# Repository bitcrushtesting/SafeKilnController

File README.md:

<!--
SPDX-FileCopyrightText: 2026 Bitcrush Testing
SPDX-License-Identifier: GPL-3.0-or-later
-->

# Safe Kiln Controller

An open-source PID controller for electric ceramic and glass kilns, built on the
**ESP32-S3** with **ESP-IDF**.

- **Simple local display**: a 128×64 OLED showing current and target temperature at a glance, plus state, segment progress and rate of rise.
- **Web interface**: served by the device itself. Live dashboard, charts of the logged data, power and energy, and the firing programs the firmware carries. **Observation only**: nothing reachable over the network can start a firing, heat the kiln or change its configuration. Those are done at the kiln.
- **PID with automatic tuning**: relay (Åström–Hägglund) autotune on the real kiln; no manual gain hunting.
- **Firing profiles are compiled in**: the device ships with its curves and nothing edits them, not over the network and not at the kiln. That removes every authoring path and the attack surface each one carries, and it has a real cost: a curve of your own means building a firmware that carries it.
- **Safety first**: thermal runaway, thermocouple failure, shorted-SSR, over-temperature and door-interlock detection, with a safety supervisor that has sole authority over a heat-enable line that decays unless actively refreshed.
- **Current monitoring**: a current transformer turns relay and element failures from slow thermal inferences into fast electrical facts, with the thermal rules retained as an independent backstop.
- **Self-contained**: no SD card, no external database, no account, no filesystem. Logs live in a circular partition on internal flash and programs in a fixed-slot one, each built so a power cut cannot tear a record; web assets are embedded in the firmware. The device makes **one** outbound connection, a daily check for a firmware update that carries nothing about the device and can be turned off at the display.
- **Designed for testability**: all decision logic is hardware-free C++ that runs on a development host against a simulated kiln.

The dashboard mid-firing. Everything on it is read from the device: the `RUN`
and `HEAT` badges, the segment progress, the logged curve. There is no button
here that changes what the kiln is doing, because there is no route behind one
(`SWR-WEB-26`), which is why both notices at the foot of the page say so
plainly.

No kiln was involved. That is the development harness of
[`host/webhost`](firmware/controller/host/webhost) running the real firmware
logic against a simulated one, and it is two commands if you want to click
around yourself:

```sh
cmake -B build-webhost -S firmware/controller/host/webhost && cmake --build build-webhost
./build-webhost/webhost --accel 60 --fire "Bisque cone 06"   # then open http://127.0.0.1:8080
```

`--fire` exists because of the read-only interface: a firing cannot be started
from the browser, so the harness starts one of the built-in examples
(`SWR-PRG-09`) through the same call the local display makes.

## Status

**In development, and not ready to fire a kiln.** The control, safety, storage,
web and interface logic is written and tested. The hardware adapters are
written and **have never been run against a board**. Two things block a
release: the field update path is specified and unbuilt, and local control,
which is now the only control, has never been operated by a person.

433 host tests on the controller and 81 on the independent safety supervisor,
all green plain and under AddressSanitizer and UBSan. `clang-tidy` is clean on
host and target with no suppressions baseline, MC/DC over the supervisor's trip
logic is 100 % against an 80 % floor, the `esp32s3` image builds with zero
warnings at 246 kB (88 % of the OTA slot free), and QEMU boots that image and
fires it. The hardware configuration, which that one compiles out, builds at
908 kB with the browser interface gzipped into it and 56 % of the slot free.

The controller is C++20; the supervisor is C++17, which is the standard
MISRA C++:2023 is written against. What is done, what is not, and what blocks
a release is [`tasklist.md`](tasklist.md), which is kept current and is the
only place that count lives.

You can watch a complete firing, and break it in a dozen ways, without any
hardware at all, see [`docs/simulation.md`](docs/simulation.md):

```sh
tools/run-qemu.sh          # the firmware on an emulated ESP32-S3, kiln simulated
```

or run the logic tests directly:

```sh
cmake -B build-host -S firmware/controller/test/host && cmake --build build-host
ctest --test-dir build-host
```

CI runs eleven jobs: the layering and licence checks, both host suites plain
and under AddressSanitizer and UBSan, a coverage gate, `clang-tidy` on host and
on target, StrictDoc over the requirements, the `esp32s3` build with a size
report and a generated bill of materials, the supervisor suites with MC/DC, the
unit design document with documentation warnings as errors, and a QEMU job that
boots the real image and asserts that the simulated kiln passes 100 degC
without latching a fault. Tagging `v*` builds a release.

## Putting a unit into production

Two tools, in this order, because the order is not interchangeable:

```sh
tools/prod-data.py flash --serial SK1-2026-000042   # identity, a plain write
tools/secure-boot.py provision --key keys/prod.pem  # dry run; add --commit
```

The production data block first, while the device is still freely writable.
Then signing, flashing and lockdown.

The two differ in what they do by default, and the difference is the point.
`prod-data.py` writes unless told `--dry-run`, because its write is a plain
flash write that a reflash undoes. `secure-boot.py` does *nothing* unless told
`--commit`, because most of what it does cannot be undone at all. Both carry a
`--self-test` that needs neither a board nor ESP-IDF.

**`secure-boot.py` burns eFuses, and three of its four steps cannot be undone.**
It refuses to touch a board until its pre-flight passes, demands a differently
worded confirmation for each irreversible step, and sequences them so the device
is left bootable at every point. Read the header of
[`firmware/controller/sdkconfig.secure`](firmware/controller/sdkconfig.secure) before the first run;
the short version is that **losing the signing key means the unit can never run
new firmware again**, and that secure boot stops hostile code running but does
nothing about secrets being read off the flash (`SRR-05`).

### Releasing an update

A third tool, for the other end of the lifecycle. The device fetches one signed
static manifest per channel and verifies it against a key compiled into its own
firmware (`SWR-UPD-09` to `SWR-UPD-16`), and this builds that manifest:

```sh
tools/update-manifest.py keygen --key keys/manifest.pem          # once, then keep it offline
tools/update-manifest.py pubkey --key keys/manifest.pem \
    --header firmware/controller/main/update_pubkey.h            # the half that ships
tools/update-manifest.py sign   --key keys/manifest.pem \
    --image build-esp32s3/safekiln.bin --version 1.4.2 \
    --security --advisory advisories/2026-002.html
tools/update-manifest.py verify --manifest dist/update/stable.json \
    --pubkey keys/manifest.pub.pem --image build-esp32s3/safekiln.bin \
    --running-version 1.4.1
```

The **bill of materials** is generated rather than written
([`tools/sbom.py`](tools/sbom.py), `SWR-NFR-28`): the component list comes from
the build's own `project_description.json`, so it names what was actually
linked, and each licence is scanned from that component's own
`SPDX-License-Identifier` tags, with anything untagged reported as
`NOASSERTION` rather than given a plausible default. CycloneDX 1.6 by default,
SPDX 2.3 with `--format spdx`, both published with every release:

```sh
tools/sbom.py --build-dir firmware/controller/build \
    --image firmware/controller/build/safekiln.bin --format both --strict
```

It has to run where `$IDF_PATH` is, which in CI means inside the IDF container
rather than a step afterwards, because a licence cannot be scanned from a tree
that is not there. The question it exists to answer is "an advisory landed this
morning against mbedTLS 3.6.0, did we ship it", and that cannot be answered
after the fact.

**The manifest key is not the secure boot key, and the tool refuses to let it
be** (`SRR-12`). The secure boot key decides what a provisioned board will
*boot* and its digest is burnt into eFuses, so it can never be rotated; this one
decides what a board will be *offered* and is used on every release. `sign` also
refuses an image with no Secure Boot V2 signature, an image whose chip id is not
this target, a version carrying build metadata, and a security release with no
advisory, because each of those produces a manifest that every device must
reject after downloading it.

It deliberately does not burn `DIS_DOWNLOAD_MODE`. Serial download is
`SWR-UPD-14`'s recovery path, for a unit whose update service is unreachable,
whose new image will not confirm itself, or which has to be downgraded; closing
it as well would make such a unit permanently unfixable.

| Document | Contents |
|---|---|
| [`docs/v-model-process.md`](docs/v-model-process.md) | The development process: the V-model levels, which document holds each, the relations between them, and an honest record of which levels exist and which do not. |
| [`docs/01_user_req.sdoc`](docs/01_user_req.sdoc) | User requirements: the target markets (the European Union), the regulatory framework that follows from them with instrument numbers and editions, the user needs with their acceptance criteria, and the project constraints. |
| [`docs/02_system_req.sdoc`](docs/02_system_req.sdoc) | System requirements: the hardware interface, the four safety requirements that hardware discharges, and the assumptions about the environment the system is placed in. |
| [`docs/03_software_req.sdoc`](docs/03_software_req.sdoc) | Software requirements: the functional, safety, non-functional and testability requirements, each with an identifier and a verification method. |
| [`docs/04_software_arch.sdoc`](docs/04_software_arch.sdoc) | Software architecture: the 22 decisions the design rests on, each with the requirement that drove it and the cost it carries. |
| [`docs/safety.sdoc`](docs/safety.sdoc) | Hazards, safety goals and residual risks, each with an identifier, and the chain between them as checked relations: which hazards a goal mitigates, which requirements realise it, and which risk its layers leave. |
| [`docs/safety.md`](docs/safety.md) | Safety concept: the system boundary, the layered protection concept and the independence claimed between layers, detection coverage and timing, the reaction and recovery sequence, and the obligations on the installer and on anyone changing the design. |
| [`docs/security.sdoc`](docs/security.sdoc) | Assets, adversaries, threats, security goals, residual risks and open questions, each with an identifier, and the chain between them as checked relations: which asset a threat is aimed at, which safety hazard it reaches, which goal answers it, and what each goal's implementation status actually is. |
| [`docs/security.md`](docs/security.md) | Security concept: scope, the attack surface and trust boundaries, the physical boundary and why the supervisor's debug port is deliberately open, the update path and why it points outwards, why a security compromise here is a safety event, what the implementation already gets right, the obligations on the owner and on whoever implements the HTTP transport, the verification status, and an inventory of what the Cyber Resilience Act still requires. |
| [`SECURITY.md`](SECURITY.md) | The security policy: where to report a vulnerability and what happens then, the single point of contact and the reporting obligations behind it, the supported versions and the support period, how a fix reaches a device, and what is already documented as a residual risk so a report need not restate it. |
| [`docs/architecture.md`](docs/architecture.md) | Architecture prose: component decomposition, task and timing design, control and safety algorithms, persistence and flash-endurance design, REST API, and the build and test architecture. |
| [`docs/test-concept.md`](docs/test-concept.md) | How the product is verified: unit, integration, system and hardware-in-the-loop, what each level can and cannot prove, the HIL fixture design, and an honest status against every testability requirement. |
| [`docs/safety-supervisor.md`](docs/safety-supervisor.md) | The independent safety supervisor (`SWA-22`): a second microcontroller holding the absolute over-temperature, thermocouple-fault and lid trips, what moves and what stays, the link, the failure modes, and the questions still open. |
| [`docs/coding-standard.md`](docs/coding-standard.md) | The coding standard: which safety standards actually reach the source code and what each asks for, the language subset and the flags that enforce it, why the supervisor contains no floating point, how a deviation is recorded, and what is not met yet. |
| [`docs/simulation.md`](docs/simulation.md) | Running the firmware against a simulated kiln, on the host and under QEMU, including fault injection. |
| [`tasklist.md`](tasklist.md) | Outstanding work, by priority. |

Start with [`docs/03_software_req.sdoc`](docs/03_software_req.sdoc); the architecture
document cites it throughout.

## Repository layout

```
docs/                  requirements, architecture, safety and security
firmware/controller/   the ESP-IDF application
firmware/supervisor/   the independent safety supervisor, STM32G031
web/                   the browser interface, served by the device
tools/                 release, provisioning, analysis and document generation
fixture/               the bed-of-nails test fixture
hardware/              schematic, PCB, pin map
housing/               enclosure
```

## Scope

Safe Kiln Controller supports **single-phase kilns only**. A three-phase kiln can be
monitored on one representative phase, but a fault confined to one of the other
two would be caught only by the thermal rules, slowly, and the power and energy
figures would cover a third of the load. Neither is a safe basis for firing a
three-phase kiln, so it is out of scope rather than partially supported.

## Hardware at a glance

| Part | Choice |
|---|---|
| MCU | ESP32-S3, ≥ 8 MB flash, no PSRAM required |
| Temperature | MAX31856 front ends, type-K. The controller reads chamber and enclosure; the **supervisor reads its own chamber couples on its own SPI buses**, so neither processor depends on the other for a temperature |
| Display | 128×64 monochrome OLED, I²C |
| Input | Rotary encoder with push button |
| Output | Zero-cross SSR in series with a safety contactor |
| Supply | **Single phase only.** One current transformer on the heater conductor |
| Door interlock | Optional normally-closed switch, stops the heater immediately when the door opens |
| Connectivity | WiFi station only. **No access point:** the network is selected and its passphrase typed at the display, so setting it up needs somebody at the kiln. mDNS (`kiln.local`) is specified and not implemented, so the device is reached by IP, which the display shows |

Details and rationale are in
[requirements §6](docs/03_software_req.sdoc).

## Credit

Functionally inspired by [**PIDKiln**](https://github.com/Saur0o0n/PIDKiln) by
Adrian Siemieniak, which showed that a low-cost ESP32 can run a real kiln well.
Safe Kiln Controller borrows its ideas, segment-based programs, dual local/web control,
on-device storage, a redundant SSR + contactor output stage, and rebuilds them
on ESP-IDF with a host-testable core and automatic PID tuning. No PIDKiln source
code is used

## Safety

Safe Kiln Controller is **not** a safety-certified device. A kiln is a multi-kilowatt mains
heater reaching temperatures at which its own wiring and the surrounding building
are at risk.

Mains wiring must be carried out by a competent person in accordance with local regulation.

The hazards, the layered protection concept and the risk that remains are
set out in [`docs/safety.md`](docs/safety.md); the requirements it derives from
are [requirements §5](docs/03_software_req.sdoc).

Safe Kiln Controller is designed for a **trusted local network** and must not be exposed
to the internet. The threat model, the controls and what is still only specified are in [`docs/security.md`](docs/security.md).

## License

GPL-3.0-or-later. See [`LICENSE`](LICENSE).

    Copyright (C) 2026 Bitcrush Testing

    This program is free software: you can redistribute it and/or modify it
    under the terms of the GNU General Public License as published by the Free
    Software Foundation, either version 3 of the License, or (at your option)
    any later version.

    This program is distributed in the hope that it will be useful, but WITHOUT
    ANY WARRANTY; without even the implied warranty of MERCHANTABILITY or
    FITNESS FOR A PARTICULAR PURPOSE.  See the GNU General Public License for
    more details.

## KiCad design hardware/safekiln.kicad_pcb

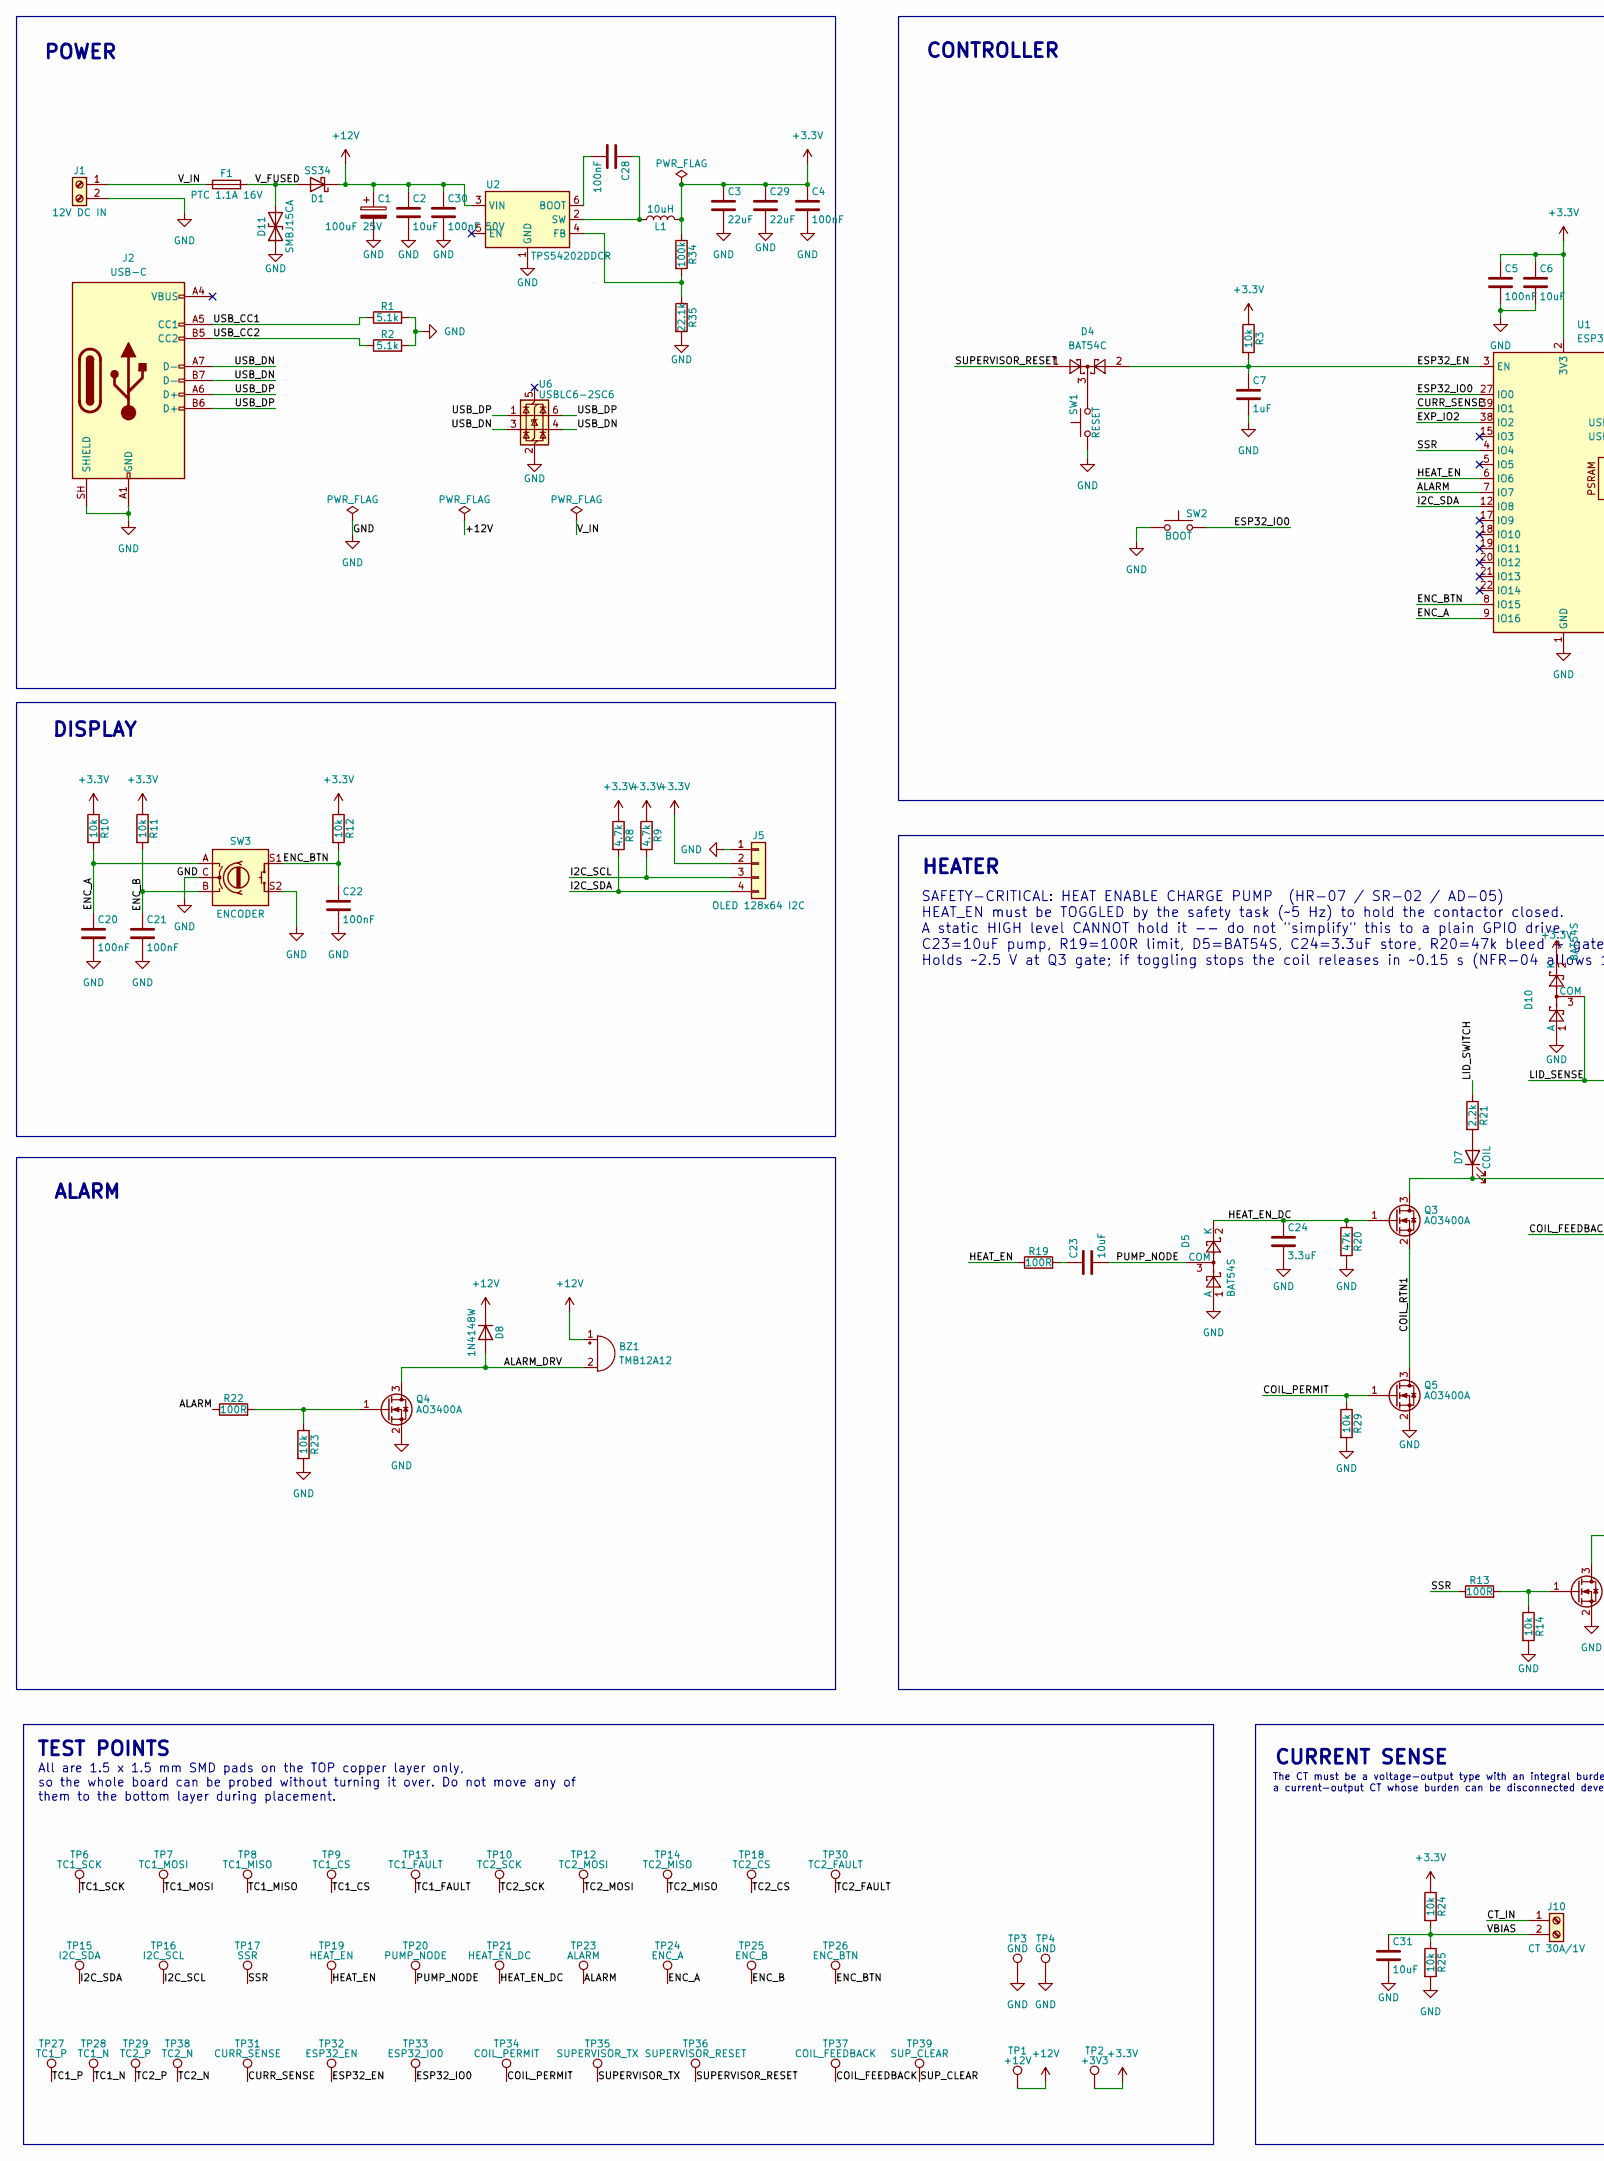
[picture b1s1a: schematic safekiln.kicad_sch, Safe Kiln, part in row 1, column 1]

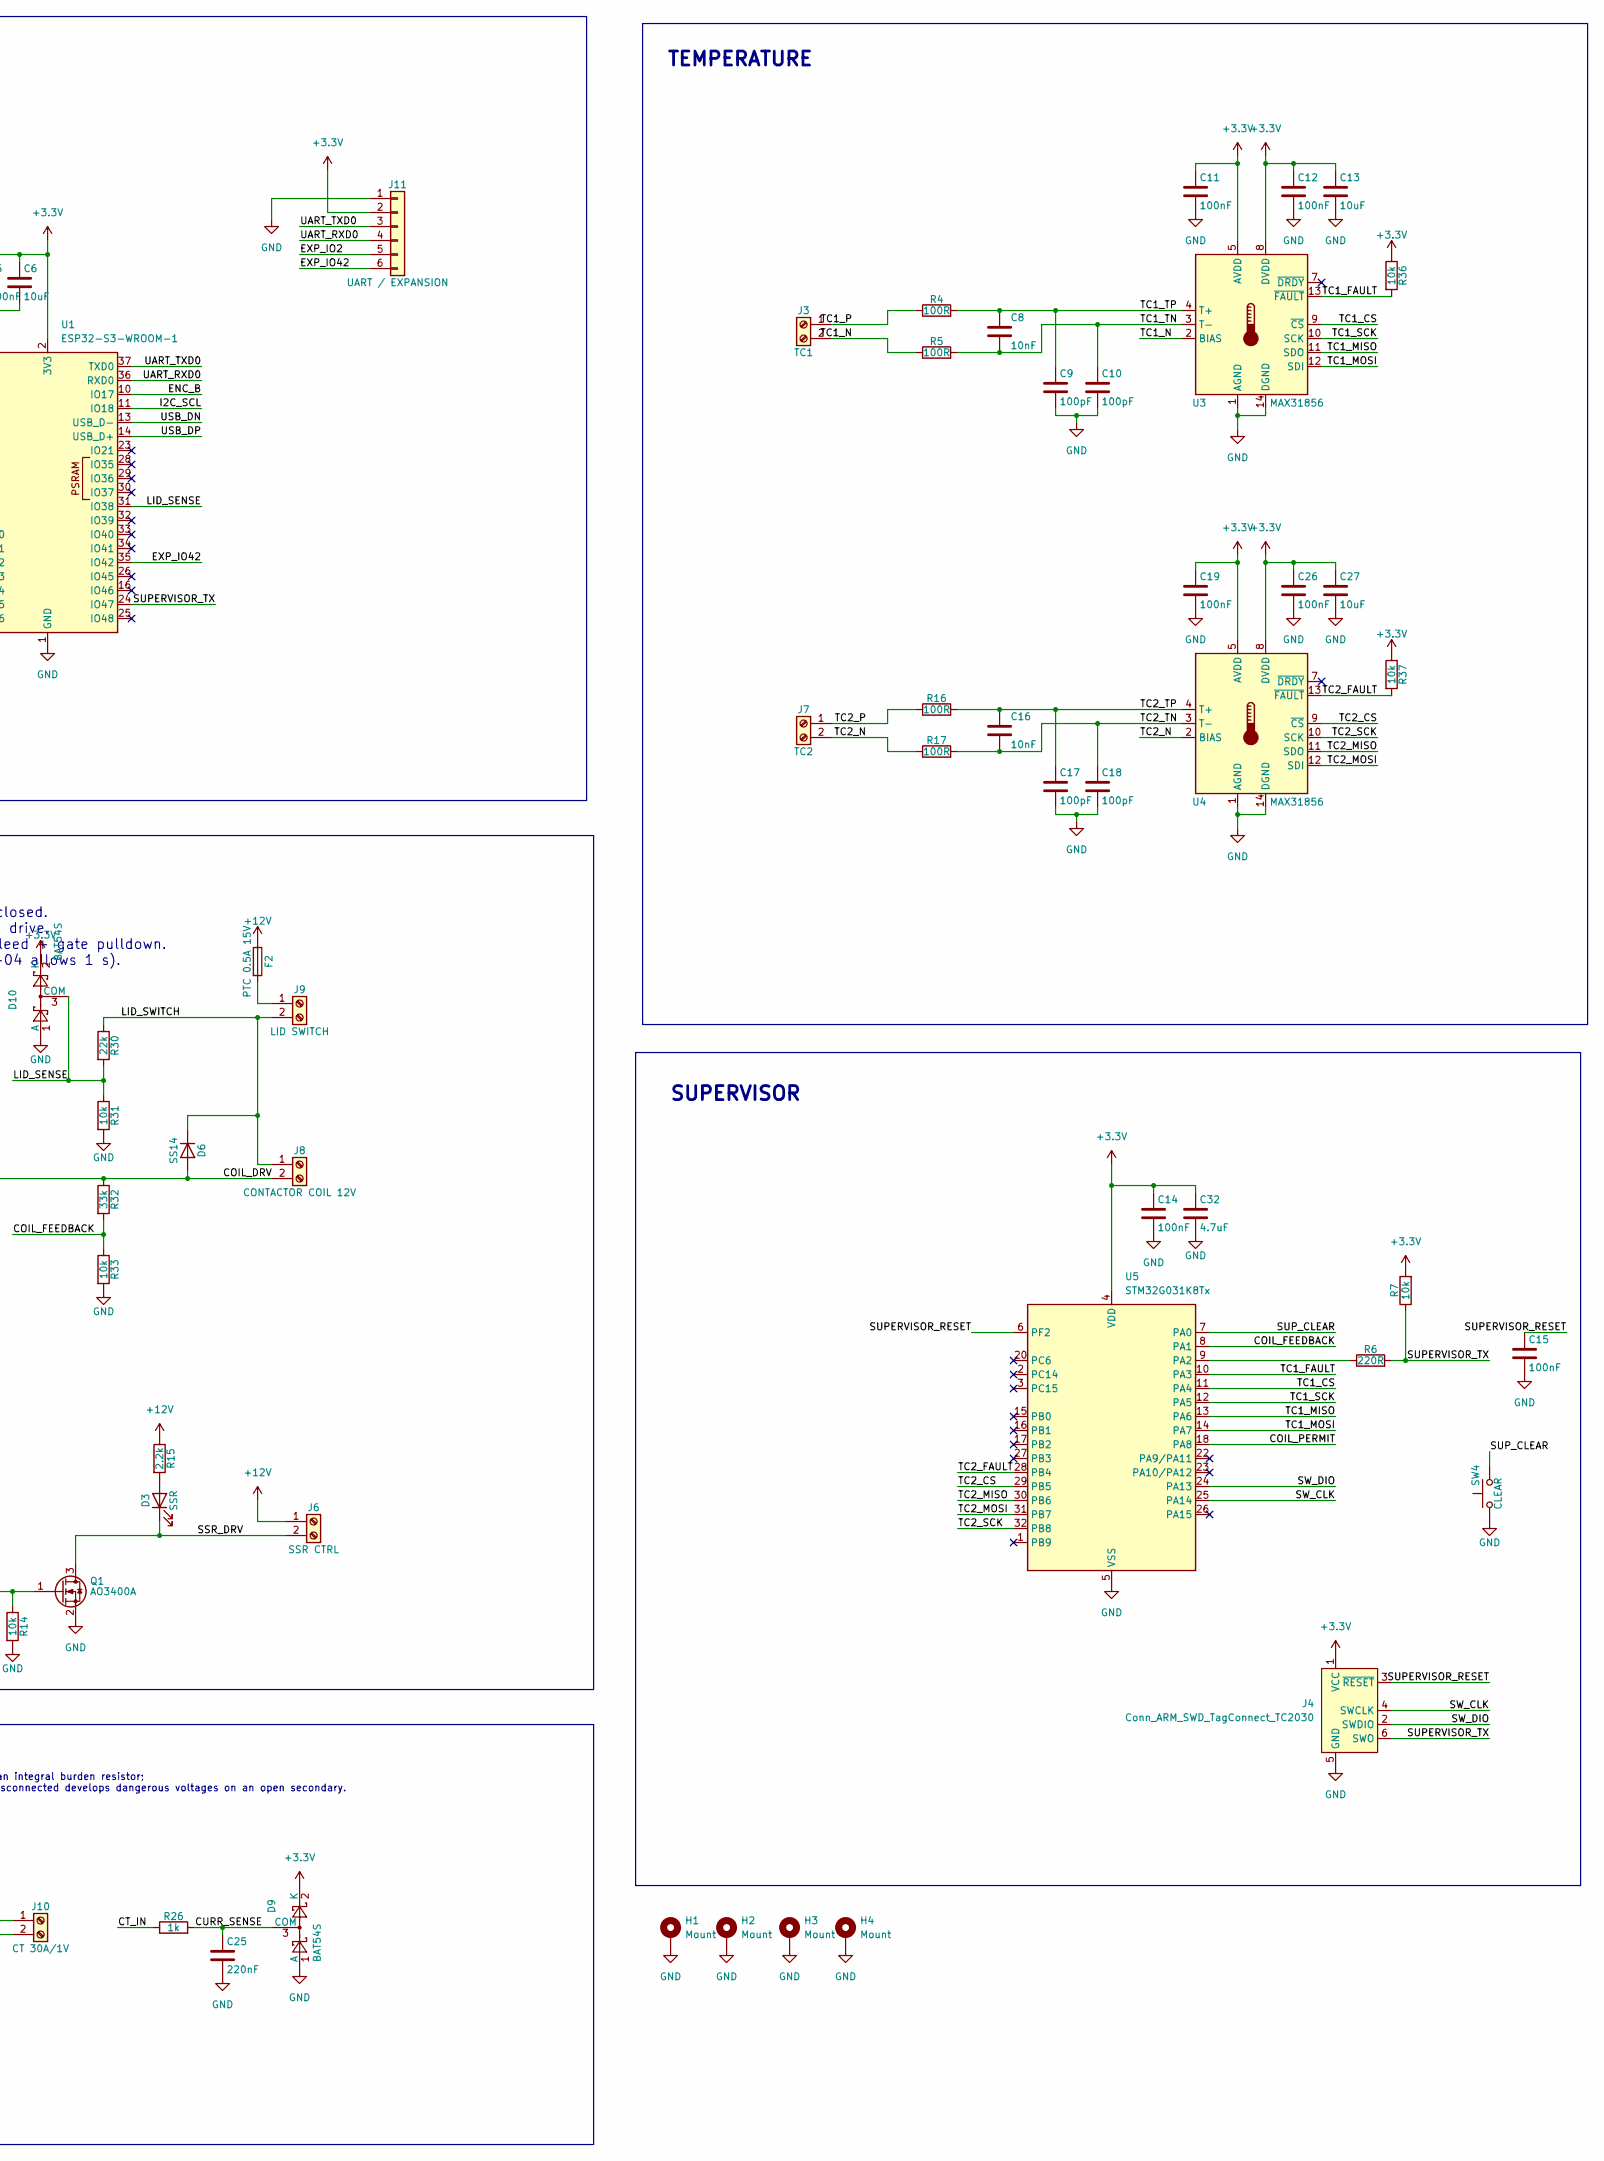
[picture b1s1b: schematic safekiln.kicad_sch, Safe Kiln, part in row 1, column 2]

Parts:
BZ1: TMB12A12; Buzzer_12x9.5RM7.6; LCSC C96079
C1: 100uF 25V; CP_Elec_6.3x7.7; LCSC C176675
C2, C6, C13, C23, C27, C31: 10uF; C_0805_2012Metric; LCSC C15850
C3, C29: 22uF; C_0805_2012Metric; LCSC C45783
C4, C5, C11, C12, C14, C15, C19, C20, C21, C22, C26, C28: 100nF; C_0402_1005Metric; LCSC C1525
C7: 1uF; C_0402_1005Metric; LCSC C52923
C8, C16: 10nF; C_0402_1005Metric; LCSC C15195
C9, C10, C17, C18: 100pF; C_0402_1005Metric; LCSC C26409
C24: 3.3uF; C_0805_2012Metric; LCSC C159781
C25: 220nF; C_0402_1005Metric; LCSC C16772
C30: 100nF 50V; C_0603_1608Metric; LCSC C14663
C32: 4.7uF; C_0603_1608Metric; LCSC C19666
D1: SS34; D_SMA; LCSC C8678
D3: SSR; LED_0603_1608Metric; LCSC C2286
D4: BAT54C; SOT-23; LCSC C236933
D5, D9, D10: BAT54S; SOT-23; LCSC C19726
D6: SS14; D_SMA; LCSC C2480
D7: COIL; LED_0603_1608Metric; LCSC C2286
D8: 1N4148W; D_SOD-123; LCSC C2099
D11: SMBJ15CA; D_SMB; LCSC C78410
F1: PTC 1.1A 16V; Fuse_1206_3216Metric; LCSC C7542961
F2: PTC 0.5A 15V; Fuse_1206_3216Metric; LCSC C151162
H1, H2, H3, H4: Mount; MountingHole_3.2mm_M3_ISO7380_Pad
J1: 12V DC IN; TerminalBlock_MaiXu_MX126-5.0-02P_1x02_P5.00mm; LCSC C474881
J2: USB-C; USB_C_Receptacle_HRO_TYPE-C-31-M-12; LCSC C165948
J3: TC1; TerminalBlock_MaiXu_MX126-5.0-02P_1x02_P5.00mm; LCSC C474881
J4: Conn_ARM_SWD_TagConnect_TC2030; Tag-Connect_TC2030-IDC-NL_2x03_P1.27mm_Vertical
J5: OLED 128x64 I2C; PinSocket_1x04_P2.54mm_Vertical
J6: SSR CTRL; TerminalBlock_MaiXu_MX126-5.0-02P_1x02_P5.00mm; LCSC C474881
J7: TC2; TerminalBlock_MaiXu_MX126-5.0-02P_1x02_P5.00mm; LCSC C474881
J8: CONTACTOR COIL 12V; TerminalBlock_MaiXu_MX126-5.0-02P_1x02_P5.00mm; LCSC C474881
J9: LID SWITCH; TerminalBlock_MaiXu_MX126-5.0-02P_1x02_P5.00mm; LCSC C474881
J10: CT 30A/1V; TerminalBlock_MaiXu_MX126-5.0-02P_1x02_P5.00mm; LCSC C474881
J11: UART / EXPANSION; PinHeader_1x06_P2.54mm_Vertical; LCSC C492405
L1: 10uH; L_Sunlord_SWPA5040S; LCSC C84608
Q1, Q3, Q4, Q5: AO3400A; SOT-23; LCSC C20917
R1, R2: 5.1k; R_0402_1005Metric; LCSC C25905
R3, R7, R10, R11, R12, R14, R23, R24, R25, R29, R31, R33, R36, R37: 10k; R_0402_1005Metric; LCSC C25744
R4, R5, R13, R16, R17, R19, R22: 100R; R_0402_1005Metric; LCSC C25076
R6: 220R; R_0402_1005Metric; LCSC C25091
R8, R9: 4.7k; R_0402_1005Metric; LCSC C25900
R15, R21: 2.2k; R_0603_1608Metric; LCSC C4190
R20: 47k; R_0402_1005Metric; LCSC C25792
R26: 1k; R_0402_1005Metric; LCSC C11702
R30: 22k; R_0402_1005Metric; LCSC C25768
R32: 33k; R_0402_1005Metric; LCSC C25779
R34: 100k; R_0402_1005Metric; LCSC C25741
R35: 22.1k; R_0402_1005Metric; LCSC C43473
SW1: RESET; SW_Push_1P1T_XKB_TS-1187A; LCSC C318884
SW2: BOOT; SW_Push_1P1T_XKB_TS-1187A; LCSC C318884
SW3: ENCODER; RotaryEncoder_Alps_EC11E-Switch_Vertical_H20mm; LCSC C7275025
SW4: CLEAR; SW_Push_1P1T_XKB_TS-1187A; LCSC C318884
TP1: +12V; TestPoint_Pad_1.5x1.5mm
TP2: +3V3; TestPoint_Pad_1.5x1.5mm
TP3, TP4: GND; TestPoint_Pad_1.5x1.5mm
TP6: TC1_SCK; TestPoint_Pad_1.5x1.5mm
TP7: TC1_MOSI; TestPoint_Pad_1.5x1.5mm
TP8: TC1_MISO; TestPoint_Pad_1.5x1.5mm
TP9: TC1_CS; TestPoint_Pad_1.5x1.5mm
TP10: TC2_SCK; TestPoint_Pad_1.5x1.5mm
TP12: TC2_MOSI; TestPoint_Pad_1.5x1.5mm
TP13: TC1_FAULT; TestPoint_Pad_1.5x1.5mm
TP14: TC2_MISO; TestPoint_Pad_1.5x1.5mm
TP15: I2C_SDA; TestPoint_Pad_1.5x1.5mm
TP16: I2C_SCL; TestPoint_Pad_1.5x1.5mm
TP17: SSR; TestPoint_Pad_1.5x1.5mm
TP18: TC2_CS; TestPoint_Pad_1.5x1.5mm
TP19: HEAT_EN; TestPoint_Pad_1.5x1.5mm
TP20: PUMP_NODE; TestPoint_Pad_1.5x1.5mm
TP21: HEAT_EN_DC; TestPoint_Pad_1.5x1.5mm
TP23: ALARM; TestPoint_Pad_1.5x1.5mm
TP24: ENC_A; TestPoint_Pad_1.5x1.5mm
TP25: ENC_B; TestPoint_Pad_1.5x1.5mm
TP26: ENC_BTN; TestPoint_Pad_1.5x1.5mm
TP27: TC1_P; TestPoint_Pad_1.5x1.5mm
TP28: TC1_N; TestPoint_Pad_1.5x1.5mm
TP29: TC2_P; TestPoint_Pad_1.5x1.5mm
TP30: TC2_FAULT; TestPoint_Pad_1.5x1.5mm
TP31: CURR_SENSE; TestPoint_Pad_1.5x1.5mm
TP32: ESP32_EN; TestPoint_Pad_1.5x1.5mm
TP33: ESP32_IO0; TestPoint_Pad_1.5x1.5mm
TP34: COIL_PERMIT; TestPoint_Pad_1.5x1.5mm
TP35: SUPERVISOR_TX; TestPoint_Pad_1.5x1.5mm
TP36: SUPERVISOR_RESET; TestPoint_Pad_1.5x1.5mm
TP37: COIL_FEEDBACK; TestPoint_Pad_1.5x1.5mm
TP38: TC2_N; TestPoint_Pad_1.5x1.5mm
TP39: SUP_CLEAR; TestPoint_Pad_1.5x1.5mm
U1: ESP32-S3-WROOM-1; LCSC C2913198
U2: TPS54202DDCR; SOT-23-6; LCSC C191884
U3, U4: MAX31856; TSSOP-14_4.4x5mm_P0.65mm; LCSC C2653162
U5: STM32G031K8Tx; LQFP-32_7x7mm_P0.8mm; LCSC C432203
U6: USBLC6-2SC6; SOT-23-6; LCSC C7519

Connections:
+3.3V: C3.1, C4.1, C5.1, C6.1, C11.1, C12.1, C13.1, C14.1, C19.1, C26.1, C27.1, C29.1, C32.1, D9.2 (K), D10.2 (K), J4.1 (VCC), J5.2, J11.2, L1.2, R3.1, R7.2, R8.1, R9.1, R10.1, R11.1, R12.1, R24.1, R34.1, R36.1, R37.1, TP2.1 (1_1), U1.2 (3V3), U3.5 (AVDD), U3.8 (DVDD), U4.5 (AVDD), U4.8 (DVDD), U5.4 (VDD)
+12V: BZ1.1 (+), C1.1, C2.1, C30.1, D1.1 (K), D8.1 (K), F2.1, J6.1, R15.1, TP1.1 (1_1), U2.3 (VIN)
/ALARM: R22.1, TP23.1 (1_1), U1.7 (IO7)
/ALARM_DRV: BZ1.2 (-), D8.2 (A), Q4.3 (D)
/COIL_DRV: D6.2 (A), D7.1 (K), J8.2, Q3.3 (D), R32.1
/COIL_FEEDBACK: R32.2, R33.1, TP37.1 (1_1), U5.8 (PA1)
/COIL_PERMIT: Q5.1 (G), R29.1, TP34.1 (1_1), U5.18 (PA8)
/COIL_RTN1: Q3.2 (S), Q5.3 (D)
/CT_IN: J10.1, R26.1
/CURR_SENSE: C25.1, D9.3 (COM), R26.2, TP31.1 (1_1), U1.39 (IO1)
/ENC_A: C20.1, R10.2, SW3.A, TP24.1 (1_1), U1.9 (IO16)
/ENC_B: C21.1, R11.2, SW3.B, TP25.1 (1_1), U1.10 (IO17)
/ENC_BTN: C22.1, R12.2, SW3.S1, TP26.1 (1_1), U1.8 (IO15)
/ESP32_EN: C7.1, D4.2, R3.2, TP32.1 (1_1), U1.3 (EN)
/ESP32_IO0: SW2.2, TP33.1 (1_1), U1.27 (IO0)
/EXP_IO2: J11.5, U1.38 (IO2)
/EXP_IO42: J11.6, U1.35 (IO42)
/HEAT_EN: R19.1, TP19.1 (1_1), U1.6 (IO6)
/HEAT_EN_DC: C24.1, D5.2 (K), Q3.1 (G), R20.1, TP21.1 (1_1)
/I2C_SCL: J5.3, R9.2, TP16.1 (1_1), U1.11 (IO18)
/I2C_SDA: J5.4, R8.2, TP15.1 (1_1), U1.12 (IO8)
/LID_SENSE: D10.3 (COM), R30.2, R31.1, U1.31 (IO38)
/LID_SWITCH: D6.1 (K), J8.1, J9.2, R21.1, R30.1
/PUMP_NODE: C23.2, D5.3 (COM), TP20.1 (1_1)
/SSR: R13.1, TP17.1 (1_1), U1.4 (IO4)
/SSR_DRV: D3.1 (K), J6.2, Q1.3 (D)
/SUPERVISOR_RESET: C15.1, D4.1, J4.3 (~RESET), TP36.1 (1_1), U5.6 (PF2)
/SUPERVISOR_TX: J4.6 (SWO), R6.2, R7.1, TP35.1 (1_1), U1.24 (IO47)
/SUP_CLEAR: SW4.2, TP39.1 (1_1), U5.7 (PA0)
/SW_CLK: J4.4 (SWCLK), U5.25 (PA14)
/SW_DIO: J4.2 (SWDIO), U5.24 (PA13)
/TC1_CS: TP9.1 (1_1), U3.9 (~CS), U5.11 (PA4)
/TC1_FAULT: R36.2, TP13.1 (1_1), U3.13 (~FAULT), U5.10 (PA3)
/TC1_MISO: TP8.1 (1_1), U3.11 (SDO), U5.13 (PA6)
/TC1_MOSI: TP7.1 (1_1), U3.12 (SDI), U5.14 (PA7)
/TC1_N: J3.2, R5.1, TP28.1 (1_1), U3.2 (BIAS)
/TC1_P: J3.1, R4.1, TP27.1 (1_1)
/TC1_SCK: TP6.1 (1_1), U3.10 (SCK), U5.12 (PA5)
/TC1_TN: C8.2, C10.1, R5.2, U3.3 (T-)
/TC1_TP: C8.1, C9.1, R4.2, U3.4 (T+)
/TC2_CS: TP18.1 (1_1), U4.9 (~CS), U5.29 (PB5)
/TC2_FAULT: R37.2, TP30.1 (1_1), U4.13 (~FAULT), U5.28 (PB4)
/TC2_MISO: TP14.1 (1_1), U4.11 (SDO), U5.30 (PB6)
/TC2_MOSI: TP12.1 (1_1), U4.12 (SDI), U5.31 (PB7)
/TC2_N: J7.2, R17.1, TP38.1 (1_1), U4.2 (BIAS)
/TC2_P: J7.1, R16.1, TP29.1 (1_1)
/TC2_SCK: TP10.1 (1_1), U4.10 (SCK), U5.32 (PB8)
/TC2_TN: C16.2, C18.1, R17.2, U4.3 (T-)
/TC2_TP: C16.1, C17.1, R16.2, U4.4 (T+)
/UART_RXD0: J11.4, U1.36 (RXD0)
/UART_TXD0: J11.3, U1.37 (TXD0)
/USB_CC1: J2.A5 (CC1), R1.1
/USB_CC2: J2.B5 (CC2), R2.1
/USB_DN: J2.A7 (D-), J2.B7 (D-), U1.13 (USB_D-), U6.3 (I/O2), U6.4 (I/O2)
/USB_DP: J2.A6 (D+), J2.B6 (D+), U1.14 (USB_D+), U6.1 (I/O1), U6.6 (I/O1)
/VBIAS: C31.1, J10.2, R24.2, R25.1
/V_FUSED: D1.2 (A), D11.2 (A2), F1.2
/V_IN: F1.1, J1.1
GND: C1.2, C2.2, C3.2, C4.2, C5.2, C6.2, C7.2, C9.2, C10.2, C11.2, C12.2, C13.2, C14.2, C15.2, C17.2, C18.2, C19.2, C20.2, C21.2, C22.2, C24.2, C25.2, C26.2, C27.2, C29.2, C30.2, C31.2, C32.2, D5.1 (A), D9.1 (A), D10.1 (A), D11.1 (A1), H1.1 (1_1), H2.1 (1_1), H3.1 (1_1), H4.1 (1_1), J1.2, J2.A1 (GND), J2.A12 (GND), J2.B1 (GND), J2.B12 (GND), J2.SH (SHIELD), J4.5 (GND), J5.1, J11.1, Q1.2 (S), Q4.2 (S), Q5.2 (S), R1.2, R2.2, R14.2, R20.2, R23.2, R25.2, R29.2, R31.2, R33.2, R35.2, SW1.1, SW2.1, SW3.C, SW3.S2, SW4.1, TP3.1 (1_1), TP4.1 (1_1), U1.1 (GND), U1.40 (GND), U1.41 (GND), U2.1 (GND), U3.1 (AGND), U3.14 (DGND), U4.1 (AGND), U4.14 (DGND), U5.5 (VSS), U6.2 (GND)
unnamed: C23.1, R19.2
unnamed: D3.2 (A), R15.2
unnamed: D4.3, SW1.2
unnamed: D7.2 (A), R21.2
unnamed: F2.2, J9.1
unnamed: Q1.1 (G), R13.2, R14.1
unnamed: Q4.1 (G), R22.2, R23.1
unnamed: C28.2, U2.6 (BOOT)
unnamed: R34.2, R35.1, U2.4 (FB)
unnamed: C28.1, L1.1, U2.2 (SW)
unnamed: R6.1, U5.9 (PA2)

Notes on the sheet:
The CT must be a voltage-output type with an integral burden resistor; a current-output CT whose burden can be disconnected develops dangerous voltages on an open secondary.
TEMPERATURE
DISPLAY
TEST POINTS
SAFETY-CRITICAL: HEAT ENABLE CHARGE PUMP (HR-07 / SR-02 / AD-05) HEAT_EN must be TOGGLED by the safety task (~5 Hz) to hold the contactor closed. A static HIGH level CANNOT hold it -- do not "simplify" this to a plain GPIO drive. C23=10uF pump, R19=100R limit, D5=BAT54S, C24=3.3uF store, R20=47k bl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
CURRENT SENSE
POWER
ALARM
HEATER
CONTROLLER
SUPERVISOR
All are 1.5 x 1.5 mm SMD pads on the TOP copper layer only, so the whole board can be probed without turning it over. Do not move any of them to the bottom layer during placement.

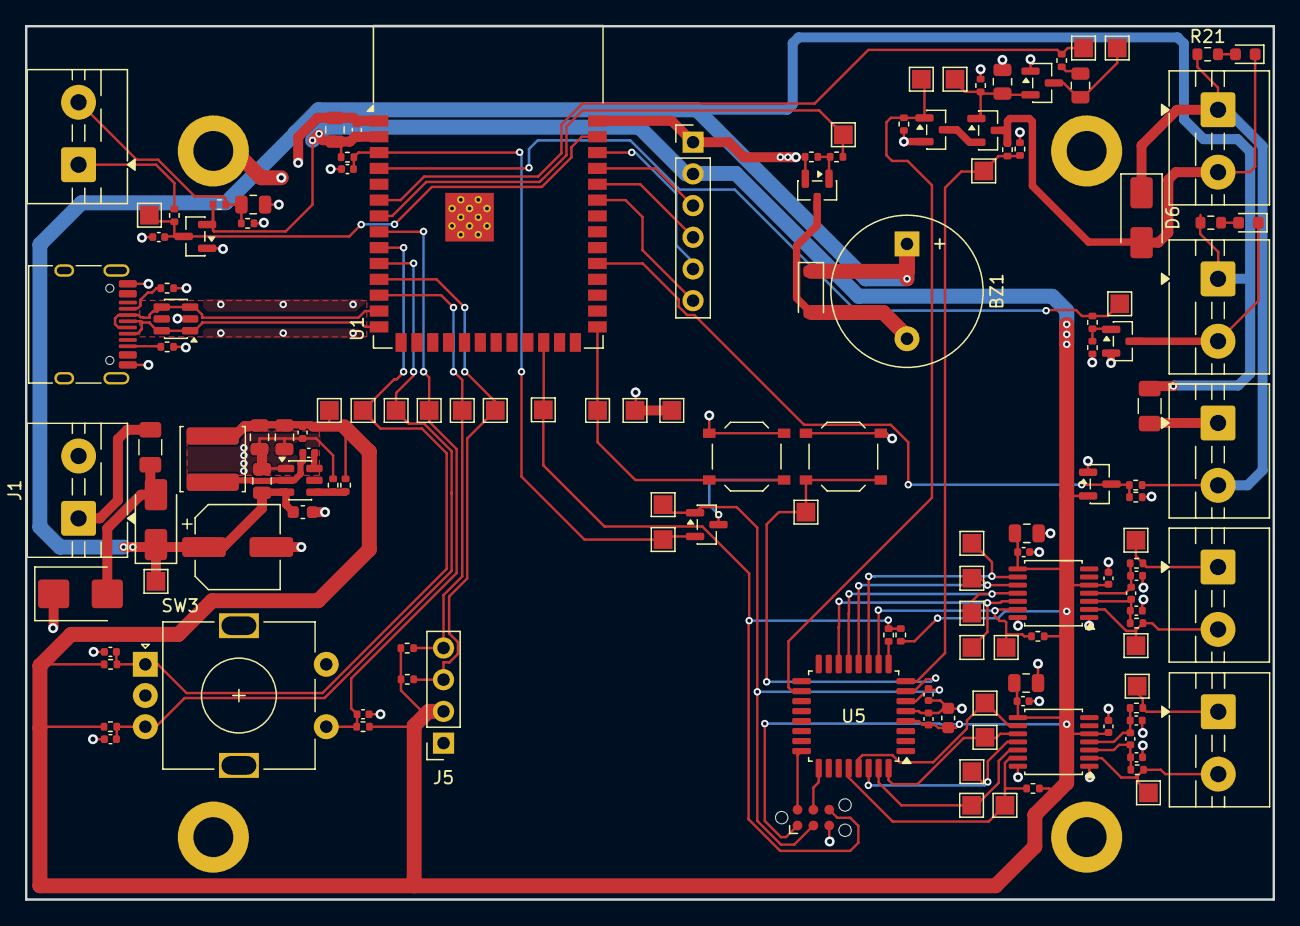
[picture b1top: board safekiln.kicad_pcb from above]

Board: 2 copper layers, 100.0 x 70.0 mm, 145 parts (1 on the bottom side), 70 nets.

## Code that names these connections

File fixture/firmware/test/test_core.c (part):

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  check(fx_uart_count == 1, "the config declares 1 uart buses");
  check(fx_i2c_count == 1, "the config declares 1 i2c buses");
  check(fx_spi_count == 1, "the config declares 1 spi buses");
  check(strcmp(fx_gpio[0].name, "tc1_cs") == 0 && fx_gpio[0].pin == 6, "tc1_cs is on GPIO6");
  check(strcmp(fx_gpio[1].name, "tc1_drdy") == 0 && fx_gpio[1].pin == 7, "tc1_drdy is on GPIO7");
  check(strcmp(fx_gpio[2].name, "tc1_fault") == 0 && fx_gpio[2].pin == 8, "tc1_fault is on GPIO8");
  check(strcmp(fx_gpio[3].name, "ssr1") == 0 && fx_gpio[3].pin == 9, "ssr1 is on GPIO9");
  check(strcmp(fx_gpio[4].name, "heat_en") == 0 && fx_gpio[4].pin == 10, "heat_en is on GPIO10");
  check(strcmp(fx_gpio[5].name, "pump_node") == 0 && fx_gpio[5].pin == 11, "pump_node is on GPIO11");
  check(strcmp(fx_gpio[6].name, "heat_en_dc") == 0 && fx_gpio[6].pin == 12, "heat_en_dc is on GPIO12");
  check(strcmp(fx_gpio[7].name, "coil_drv") == 0 && fx_gpio[7].pin == 13, "coil_drv is on GPIO13");
  check(strcmp(fx_gpio[8].name, "alarm") == 0 && fx_gpio[8].pin == 14, "alarm is on GPIO14");
  check(strcmp(fx_gpio[9].name, "enc_a") == 0 && fx_gpio[9].pin == 15, "enc_a is on GPIO15");
  check(strcmp(fx_gpio[10].name, "enc_b") == 0 && fx_gpio[10].pin == 16, "enc_b is on GPIO16");
  check(strcmp(fx_gpio[11].name, "enc_btn") == 0 && fx_gpio[11].pin == 17, "enc_btn is on GPIO17");
  check(strcmp(fx_gpio[12].name, "tc1_p") == 0 && fx_gpio[12].pin == 18, "tc1_p is on GPIO18");
  check(strcmp(fx_gpio[13].name, "tc1_n") == 0 && fx_gpio[13].pin == 19, "tc1_n is on GPIO19");
  check(strcmp(fx_gpio[14].name, "curr_sense") == 0 && fx_gpio[14].pin == 20, "curr_sense is on GPIO20");
  check(strcmp(fx_gpio[15].name, "esp32_en") == 0 && fx_gpio[15].pin == 21, "esp32_en is on GPIO21");
  check(strcmp(fx_gpio[16].name, "esp32_io0") == 0 && fx_gpio[16].pin == 22, "esp32_io0 is on GPIO22");
  check(strcmp(fx_gpio[17].name, "coil_permit") == 0 && fx_gpio[17].pin == 23, "coil_permit is on GPIO23");
  check(strcmp(fx_gpio[18].name, "supervisor_reset") == 0 && fx_gpio[18].pin == 24, "supervisor_reset is on GPIO24");
  check(strcmp(fx_adc[0].name, "ch_5v") == 0 && fx_adc[0].adc == 0, "ch_5v reads ADC0");
  check(strcmp(fx_adc[1].name, "ch_3_3v") == 0 && fx_adc[1].adc == 1, "ch_3_3v reads ADC1");
  check(strcmp(fx_uart[0].name, "supervisor_uart") == 0 && fx_uart[0].index == 0, "supervisor_uart is uart0");
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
